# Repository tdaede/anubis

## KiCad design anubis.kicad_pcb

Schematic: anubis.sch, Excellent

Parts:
C1, C2, C3, C4: 0.1uF; C_0805_2012Metric_Pad1.15x1.40mm_HandSolder
J1, J2: Conn_02x20_Odd_Even; PinSocket_2x20_P2.54mm_Vertical
R1, R2: 10K; R_0805_2012Metric_Pad1.15x1.40mm_HandSolder
U1, U2, U3, U4, U5, U6, U7, U8: SN74LVC8T245DWR; SOIC-24W_7.5x15.4mm_P1.27mm
U9: 74LS05; SOIC-14_3.9x8.7mm_P1.27mm
U10: 68000D; DIP-64_750_ELL

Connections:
+3V3: C3.1, C4.1, J1.1, J1.2, J1.19, J1.20, J1.39, J1.40, J2.1, J2.2, J2.19, J2.20, U1.1 (VCCA), U2.1 (VCCA), U3.1 (VCCA), U4.1 (VCCA), U5.1 (VCCA), U6.1 (VCCA), U7.1 (VCCA), U8.1 (VCCA), U9.14 (VCC)
+5V: C1.1, C2.1, J2.40, U1.23 (VCCB), U1.24 (VCCB), U2.23 (VCCB), U2.24 (VCCB), U3.23 (VCCB), U3.24 (VCCB), U4.23 (VCCB), U4.24 (VCCB), U5.23 (VCCB), U5.24 (VCCB), U6.23 (VCCB), U6.24 (VCCB), U7.23 (VCCB), U7.24 (VCCB), U8.23 (VCCB), U8.24 (VCCB), U10.14 (VCC), U10.49 (VCC)
/addr_dir: J2.9, R1.1, U2.2 (DIR), U4.2 (DIR), U6.2 (DIR), U7.2 (DIR), U8.2 (DIR)
/data_dir: R2.1, U1.2 (DIR), U5.2 (DIR), U9.4
/mb_a1: U2.20 (B2), U10.29 (A1)
/mb_a2: U2.19 (B3), U10.30 (A2)
/mb_a3: U2.18 (B4), U10.31 (A3)
/mb_a4: U2.17 (B5), U10.32 (A4)
/mb_a5: U2.16 (B6), U10.33 (A5)
/mb_a6: U2.15 (B7), U10.34 (A6)
/mb_a7: U2.14 (B8), U10.35 (A7)
/mb_a8: U8.21 (B1), U10.36 (A8)
/mb_a9: U8.20 (B2), U10.37 (A9)
/mb_a10: U8.19 (B3), U10.38 (A10)
/mb_a11: U8.18 (B4), U10.39 (A11)
/mb_a12: U8.17 (B5), U10.40 (A12)
/mb_a13: U8.16 (B6), U10.41 (A13)
/mb_a14: U8.15 (B7), U10.42 (A14)
/mb_a15: U8.14 (B8), U10.43 (A15)
/mb_a16: U6.21 (B1), U10.44 (A16)
/mb_a17: U6.20 (B2), U10.45 (A17)
/mb_a18: U6.19 (B3), U10.46 (A18)
/mb_a19: U6.18 (B4), U10.47 (A19)
/mb_a20: U6.17 (B5), U10.48 (A20)
/mb_a21: U6.16 (B6), U10.50 (A21)
/mb_a22: U6.15 (B7), U10.51 (A22)
/mb_a23: U6.14 (B8), U10.52 (A23)
/mb_as: U4.21 (B1), U10.6 (AS)
/mb_berr: U10.22 (BERR)
/mb_bg: U9.2, U10.11 (BG)
/mb_bgack: U3.21 (B1), U10.12 (BGACK)
/mb_br: U3.20 (B2), U10.13 (BR)
/mb_clk: U3.19 (B3), U10.15 (CLK)
/mb_d0: U1.14 (B8), U10.5 (D0)
/mb_d1: U1.15 (B7), U10.4 (D1)
/mb_d2: U1.16 (B6), U10.3 (D2)
/mb_d3: U1.17 (B5), U10.2 (D3)
/mb_d4: U1.18 (B4), U10.1 (D4)
/mb_d5: U1.19 (B3), U10.64 (D5)
/mb_d6: U1.20 (B2), U10.63 (D6)
/mb_d7: U1.21 (B1), U10.62 (D7)
/mb_d8: U5.14 (B8), U10.61 (D8)
/mb_d9: U5.15 (B7), U10.60 (D9)
/mb_d10: U5.16 (B6), U10.59 (D10)
/mb_d11: U5.17 (B5), U10.58 (D11)
/mb_d12: U5.18 (B4), U10.57 (D12)
/mb_d13: U5.19 (B3), U10.56 (D13)
/mb_d14: U5.20 (B2), U10.55 (D14)
/mb_d15: U5.21 (B1), U10.54 (D15)
/mb_dtack: U7.17 (B5), U10.10 (DTACK)
/mb_e: U10.20 (E)
/mb_fc0: U7.19 (B3), U10.28 (FC0)
/mb_fc1: U7.20 (B2), U10.27 (FC1)
/mb_fc2: U7.21 (B1), U10.26 (FC2)
/mb_halt: U3.18 (B4), U10.17 (HALT)
/mb_ipl0: U3.14 (B8), U10.25 (IPL0)
/mb_ipl1: U3.15 (B7), U10.24 (IPL1)
/mb_ipl2: U3.16 (B6), U10.23 (IPL2)
/mb_lds: U4.19 (B3), U10.8 (LDS)
/mb_reset: U3.17 (B5), U10.18 (RESET)
/mb_rw: U4.18 (B4), U10.9 (R/W)
/mb_uds: U4.20 (B2), U10.7 (UDS)
/mb_vma: U10.19 (VMA)
/mb_vpa: U10.21 (VPA)
/ulx_a1: J2.30, U2.4 (A2)
/ulx_a2: J2.31, U2.5 (A3)
/ulx_a3: J2.32, U2.6 (A4)
/ulx_a4: J2.33, U2.7 (A5)
/ulx_a5: J2.34, U2.8 (A6)
/ulx_a6: J2.35, U2.9 (A7)
/ulx_a7: J2.36, U2.10 (A8)
/ulx_a8: J1.5, U8.3 (A1)
/ulx_a9: J1.6, U8.4 (A2)
/ulx_a10: J1.7, U8.5 (A3)
/ulx_a11: J1.8, U8.6 (A4)
/ulx_a12: J1.9, U8.7 (A5)
/ulx_a13: J1.10, U8.8 (A6)
/ulx_a14: J1.11, U8.9 (A7)
/ulx_a15: J1.12, U8.10 (A8)
/ulx_a16: J1.16, U6.3 (A1)
/ulx_a17: J1.17, U6.4 (A2)
/ulx_a18: J1.18, U6.5 (A3)
/ulx_a19: J1.23, U6.6 (A4)
/ulx_a20: J1.24, U6.7 (A5)
/ulx_a21: J1.25, U6.8 (A6)
/ulx_a22: J1.26, U6.9 (A7)
/ulx_a23: J1.27, U6.10 (A8)
/ulx_as: J2.8, U4.3 (A1)
/ulx_bg: J2.10, U9.1
/ulx_bgack: J2.23, U3.3 (A1)
/ulx_br: J2.24, U3.4 (A2)
/ulx_clk: J2.25, U3.5 (A3)
/ulx_d0: J2.18, U1.10 (A8)
/ulx_d1: J2.17, U1.9 (A7)
/ulx_d2: J2.16, U1.8 (A6)
/ulx_d3: J2.15, U1.7 (A5)
/ulx_d4: J2.14, U1.6 (A4)
/ulx_d5: J2.13, U1.5 (A3)
/ulx_d6: J2.12, U1.4 (A2)
/ulx_d7: J2.11, U1.3 (A1)
/ulx_d8: J1.29, U5.3 (A1)
/ulx_d9: J1.30, U5.4 (A2)
/ulx_d10: J1.31, U5.5 (A3)
/ulx_d11: J1.32, U5.6 (A4)
/ulx_d12: J1.33, U5.7 (A5)
/ulx_d13: J1.34, U5.8 (A6)
/ulx_d14: J1.35, U5.9 (A7)
/ulx_d15: J1.36, U5.10 (A8)
/ulx_dtack: J1.28, U7.7 (A5)
/ulx_fc0: J1.15, U7.5 (A3)
/ulx_fc1: J1.14, U7.4 (A2)
/ulx_fc2: J1.13, U7.3 (A1)
/ulx_halt: U3.6 (A4)
/ulx_ipl0: J2.29, U3.10 (A8)
/ulx_ipl1: J2.28, U3.9 (A7)
/ulx_ipl2: J2.27, U3.8 (A6)
/ulx_lds: J2.5, U4.5 (A3)
/ulx_reset: J2.26, U3.7 (A5)
/ulx_rw: J2.6, U4.6 (A4), U9.3
/ulx_uds: J2.7, U4.4 (A2)
GND: C1.2, C2.2, C3.2, C4.2, J1.3, J1.4, J1.21, J1.22, J1.37, J1.38, J2.3, J2.4, J2.21, J2.22, J2.37, J2.38, R1.2, R2.2, U1.11 (GND), U1.12 (GND), U1.13 (GND), U2.11 (GND), U2.12 (GND), U2.13 (GND), U2.22 (OE), U3.2 (DIR), U3.11 (GND), U3.12 (GND), U3.13 (GND), U4.11 (GND), U4.12 (GND), U4.13 (GND), U4.22 (OE), U5.11 (GND), U5.12 (GND), U5.13 (GND), U6.11 (GND), U6.12 (GND), U6.13 (GND), U6.22 (OE), U7.11 (GND), U7.12 (GND), U7.13 (GND), U8.11 (GND), U8.12 (GND), U8.13 (GND), U8.22 (OE), U9.5, U9.7 (GND), U9.9, U9.11, U9.13, U10.16 (GND), U10.53 (GND)

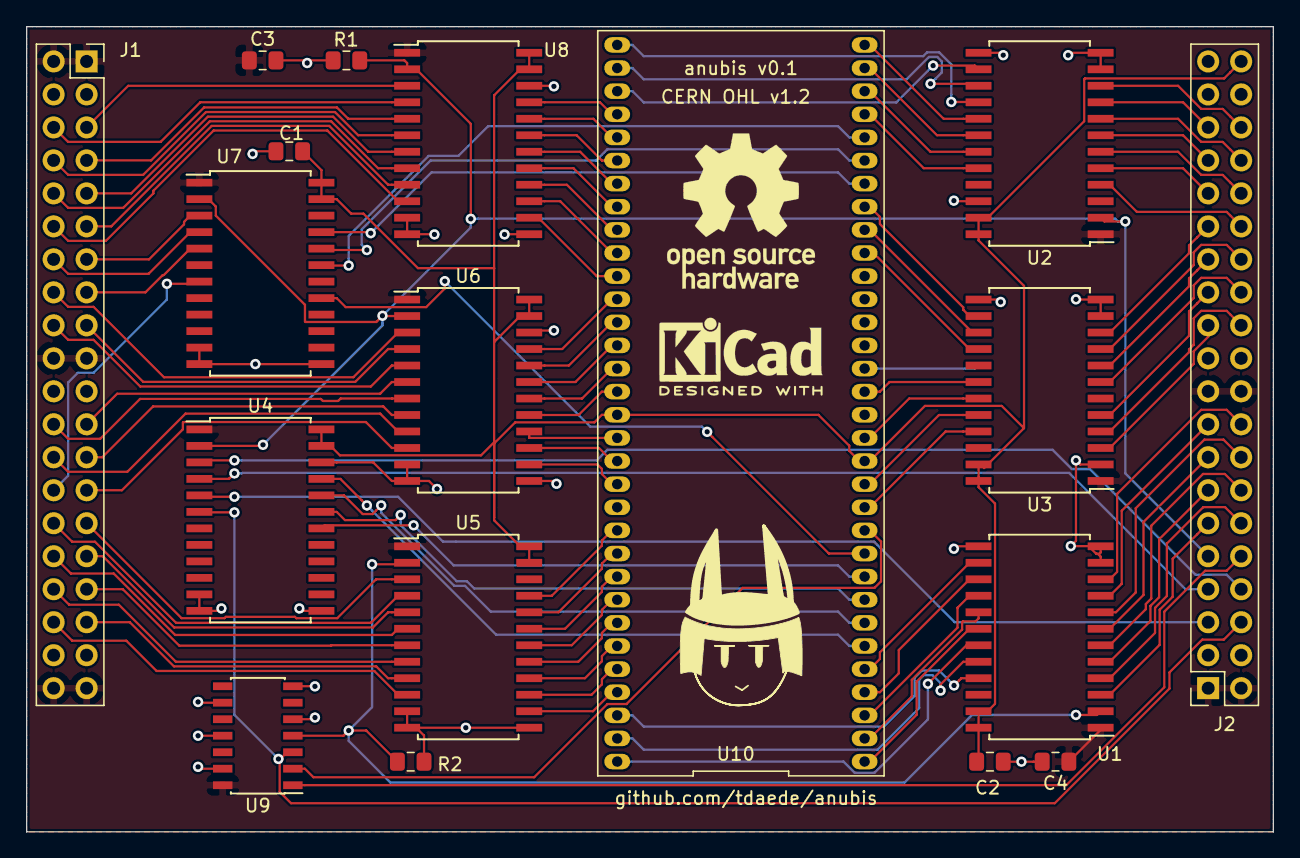
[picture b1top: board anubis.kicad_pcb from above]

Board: 2 copper layers, 96.0 x 62.0 mm, 20 parts (0 on the bottom side), 116 nets.

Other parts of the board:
svg2mod, svg2mod#2: G***; anubis_logo

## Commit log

2018-11-10 add 68040
2018-11-10 add dcm
2018-11-10 wire up 646's
2019-03-27 asdf
2019-04-03 make it good
2020-09-27 add missing files
2020-11-29 fix some part numbers

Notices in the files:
anubis.kicad_pcb:
CERN OHL v1.2
